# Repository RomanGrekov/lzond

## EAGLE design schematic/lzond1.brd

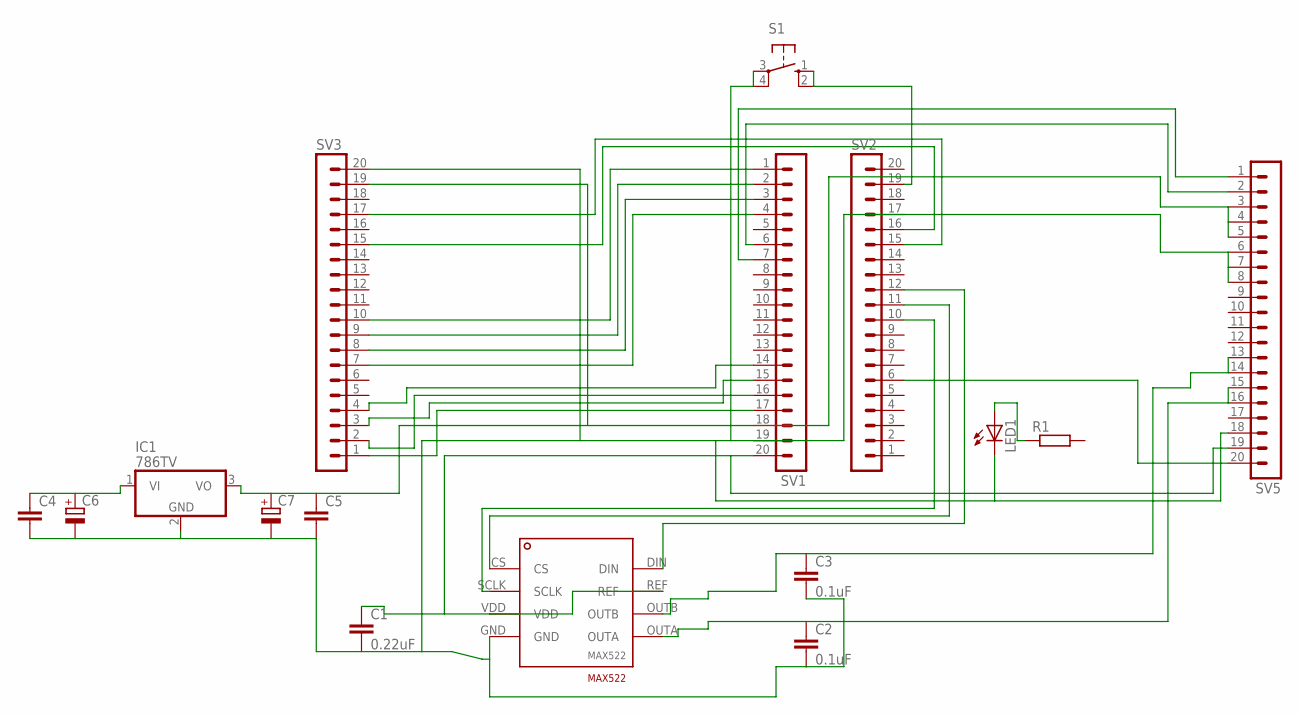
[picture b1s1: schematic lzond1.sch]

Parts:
C1: 0.22uF; C0805
C2, C3: 0.1uF; C0805
C4, C5: C-EUC1210; C1210
C6, C7: CPOL-EUE5-8.5; E5-8,5
IC1: 786TV; TO220V
LED1: LED3MM
R1: R-EU_R0805; R0805
S1: 10-XX; B3F-10XX
SV1, SV2, SV3, SV5: MA20-1
U$2: MAX522

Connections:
unnamed: SV1.4, SV3.7
unnamed: SV1.3, SV3.8
unnamed: SV1.2, SV3.9
unnamed: C4.1, C6.+, IC1.1 (VI)
unnamed: SV1.1, SV3.10
unnamed: C1.1, SV1.20, SV5.19, U$2.REF, U$2.VDD
unnamed: LED1.A, R1.1
unnamed: C1.2, C2.2, C3.2, C4.2, C5.2, C6.-, C7.-, IC1.2 (GND), LED1.K (C), S1.3, S1.4 (P1), SV1.19, SV3.20, SV5.6, SV5.7, SV5.8, SV5.18, U$2.GND
unnamed: SV2.16, SV3.15
unnamed: SV2.15, SV3.17
unnamed: SV1.6, SV5.2
unnamed: SV2.12, U$2.DIN
unnamed: SV2.11, U$2.CS
unnamed: SV2.10, U$2.SCLK
unnamed: S1.1 (S), S1.2 (S1), SV2.19
unnamed: SV1.7, SV5.1
unnamed: SV2.6, SV5.20
unnamed: SV1.17, SV3.1
unnamed: C5.1, C7.+, IC1.3 (VO), SV1.18, SV3.19, SV5.3, SV5.4, SV5.5
unnamed: SV1.16, SV3.2
unnamed: SV1.15, SV3.3
unnamed: SV1.14, SV3.4
unnamed: C3.1, SV5.13, SV5.14, U$2.OUTB
unnamed: C2.1, SV5.15, SV5.16, U$2.OUTA

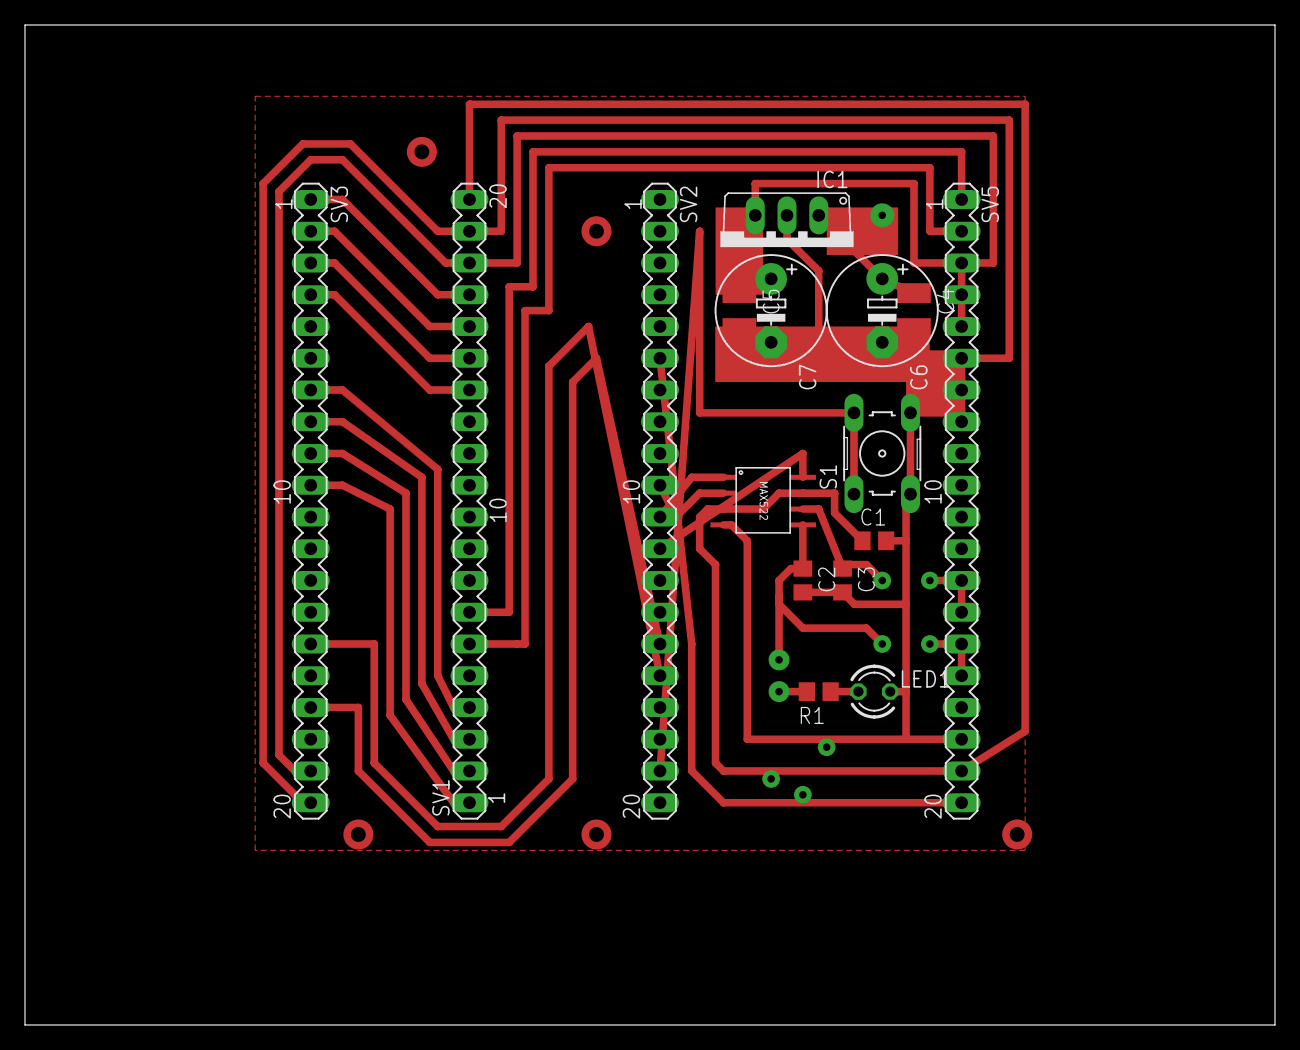
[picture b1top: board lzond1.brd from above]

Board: 2 copper layers, 100.0 x 80.0 mm, 16 parts (0 on the bottom side), 24 nets.

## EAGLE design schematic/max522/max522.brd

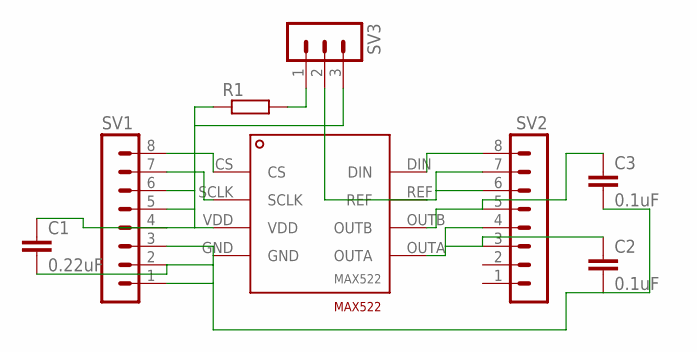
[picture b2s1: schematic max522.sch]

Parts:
C1: 0.22uF; C0805
C2, C3: 0.1uF; C0805
R1: R-EU_M0805; M0805
SV1, SV2: MA08-1
SV3: MA03-1
U$1: MAX522

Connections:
unnamed: SV1.8, U$1.CS
unnamed: SV1.7, U$1.SCLK
unnamed: C1.1, R1.1, SV1.4, SV1.5, SV1.6, SV3.3, U$1.VDD
unnamed: C1.2, C2.2, C3.2, SV1.1, SV1.2, SV1.3, U$1.GND
unnamed: SV2.8, U$1.DIN
unnamed: SV2.6, SV2.7, SV3.2, U$1.REF
unnamed: C3.1, SV2.5, U$1.OUTB
unnamed: C2.1, SV2.3, SV2.4, U$1.OUTA
unnamed: R1.2, SV3.1

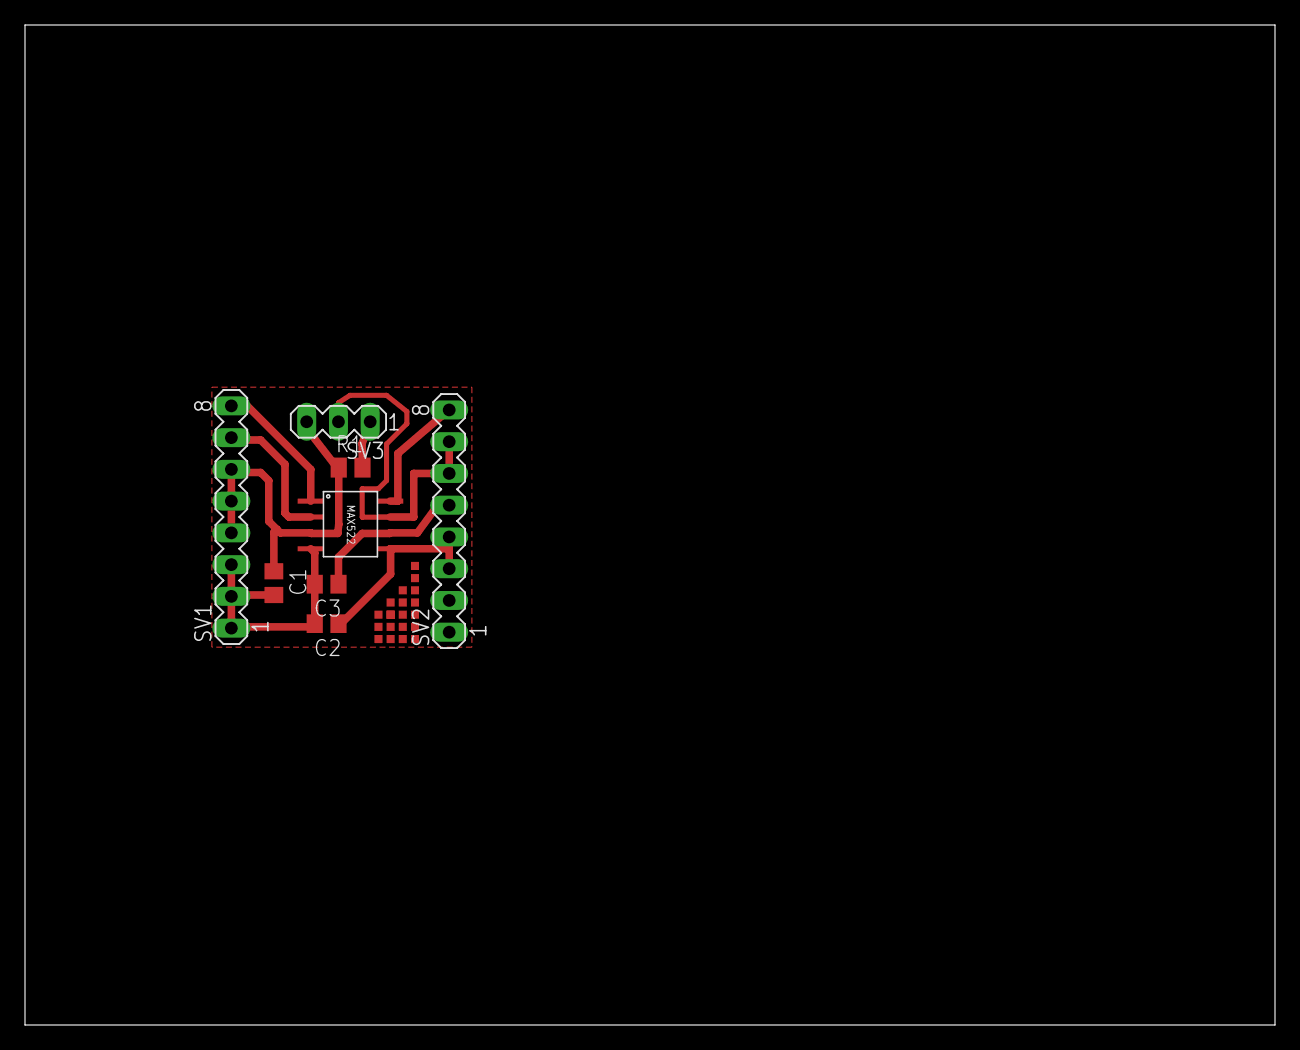
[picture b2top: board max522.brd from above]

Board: 2 copper layers, 100.0 x 80.0 mm, 8 parts (0 on the bottom side), 9 nets.

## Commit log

2015-05-27 Fixed params store
2015-05-28 Fixed params save and button state switch
2015-06-06 Refactored buttons and commands
2015-06-06 Added gitignore
2015-06-06 Refactored configurator
2015-06-23 Added dac_logic
2015-06-25 Added MAX522 shield schema
2015-07-03 added libs for spi. changed dac.c
2015-07-08 Finished DAC functions
2015-07-12 Added steps in adc logic
2015-07-15 Added get_half_period. Need to be tested
2015-07-15 Finished get_half_period
2015-07-15 Added xprintf
2015-07-16 Changed log to xprintf
2015-07-16 Removed string_lib
2015-07-16 Removed string_lib includes in modules
2015-07-16 Added stage 2
2015-07-17 Finished main part. Need to add main values to LCD
2015-07-17 Added displaing few argumets to LCD
2015-07-19 Fixed some little bugs in logic
2015-07-21 Added lzond dev board scheme
2015-07-28 Fixed bug in mix definition
2015-07-28 Full logic refactoring
2015-07-30 Added pc program. Refactored a lot of code
2015-07-31 Change algoritm
2015-08-01 Full dac logic refactoring
2015-08-01 Fixed small bugs
2015-08-02 Finished main part of lzond_manager
2015-08-04 Small changes
2015-08-04 Added new commands to logic
